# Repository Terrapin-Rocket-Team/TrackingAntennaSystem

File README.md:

# TrackingAntennaSystem
Repository will store all resources for the tracking antenna system which will dynamically point at the rocket mid-flight.

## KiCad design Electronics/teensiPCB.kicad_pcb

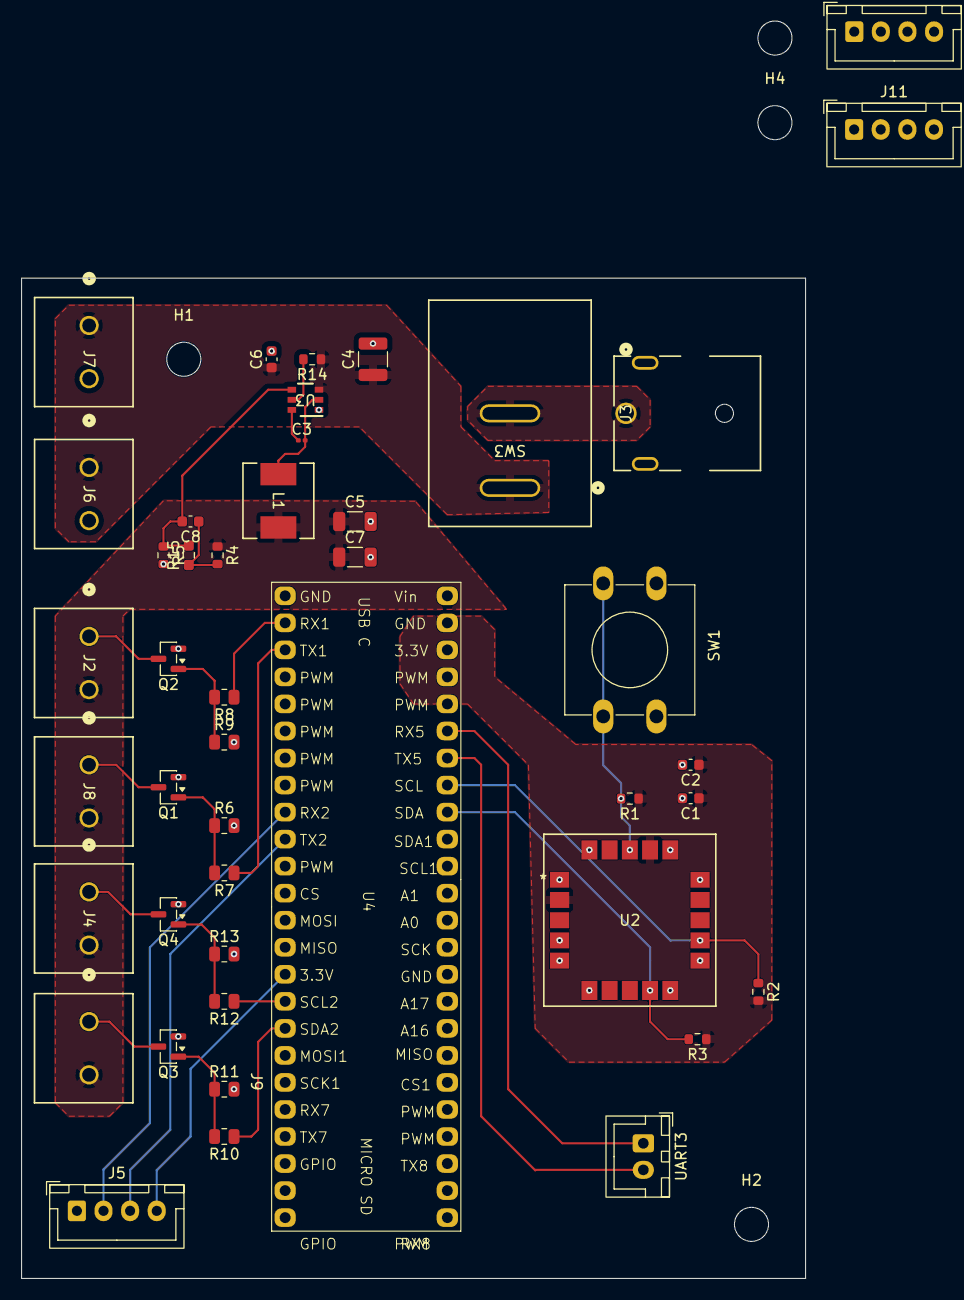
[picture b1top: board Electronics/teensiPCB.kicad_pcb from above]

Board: 2 copper layers, 73.7 x 94.0 mm, 48 parts (0 on the bottom side), 31 nets.

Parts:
C1: 0.1uF; C_0603_1608Metric
C2: 1uF; C_0603_1608Metric
C3: .1 uF; C_0201_0603Metric
C4: 10 uF; C_1210_3225Metric
C5, C7: 22 uF; C_1206_3216Metric
C6: .1 uF; C_0603_1608Metric
C8: 75 pF; C_0603_1608Metric
H1, H2, H3, H4: MountingHole; MountingHole_3.2mm_M3
J2, J8: 5V_logic_1; CONN_1935161_PXC
J3: Jack-DC; CONN1x2_PJ-082BH_CUD
J4, J9: 5V_logic_2; CONN_1935161_PXC
J5: UART1; JST_XH_B4B-XH-A_1x04_P2.50mm_Vertical
J6, J7: 24V_power_output; CONN_1935161_PXC
J10: UART2; JST_XH_B4B-XH-A_1x04_P2.50mm_Vertical
J11: 12C; JST_XH_B4B-XH-A_1x04_P2.50mm_Vertical
L1: 15 uH; IND_PCC-M0630M-LP_PAN
Q1, Q2, Q3, Q4: AO3400A; SOT-23
R1, R2, R3: 4.7k; R_0603_1608Metric
R4: 49.9 Ohms; R_0603_1608Metric
R5: 13.3 kOhms; R_0603_1608Metric
R6, R9, R11, R13: 10kO; R_0805_2012Metric
R7, R8, R10, R12: 330 Ohm; R_0805_2012Metric
R14: 510 kOhms; R_0603_1608Metric
R15: 100 kOhms; R_0603_1608Metric_Pad0.98x0.95mm_HandSolder
SW1: SW_Push; SW_PUSH-12mm
SW3: SW_SPST; SMT_1131121_EWI
U2: SAM-M10Q-00B; SAM-M10Q_UBL
U3: TPS54202HDDCR; DDC0006A_L
U4: Teensy4.1; teensy
UART3: Conn_01x02; JST_XH_B2B-XH-A_1x02_P2.50mm_Vertical

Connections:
5_dir-_1: J2.1, Q2.3 (D)
5_dir-_2: J4.1, Q4.3 (D)
5_pul-_1: J8.1, Q1.3 (D)
5_pul-_2: J9.1, Q3.3 (D)
33_dir-_1: R8.1, U4.2 (0_RX1_CRX2_CS1)
33_dir-_2: R12.1, U4.16 (24_A10_TX6_SCL2)
33_pul-_1: R7.1, U4.3 (1_TX1_CTX2_MISO1)
33_pul-_2: R10.1, U4.17 (25_A11_RX6_SDA2)
+3V3: C1.1, C2.1, J5.4, J10.4, J11.4, R1.1, R2.2, R3.1, U2.2 (V_IO), U2.17 (VCC)
+5V: C5.1, C7.1, J2.2, J4.2, J8.2, J9.2, L1.2, R4.1
+24V: C4.1, C6.1, J6.1, J7.1, R14.1, SW3.2 (B), U3.3 (VIN)
GND: C1.2, C2.2, C4.2, C5.2, C6.2, C7.2, J3.2, J5.1, J6.2, J7.2, J10.1, J11.1, Q1.2 (S), Q2.2 (S), Q3.2 (S), Q4.2 (S), R5.2, R6.2, R9.2, R11.2, R13.2, SW1.1, U2.1 (GND), U2.4 (GND), U2.5 (GND), U2.6 (GND), U2.10 (GND), U2.11 (GND), U2.15 (GND), U2.16 (GND), U2.20 (GND), U3.1 (GND)
GPS_SCL: R2.1, U2.12 (SCL), U4.41 (19_A5_SCL)
GPS_SDA: R3.2, U2.9 (SDA), U4.40 (18_A4_SDA)
unnamed: C8.1, R4.2, R15.1
unnamed: Q1.1 (G), R6.1, R7.2
unnamed: Q2.1 (G), R8.2, R9.1
unnamed: Q3.1 (G), R10.2, R11.1
unnamed: Q4.1 (G), R12.2, R13.1
unnamed: J3.1, SW3.1 (A)
unnamed: R1.2, SW1.2, U2.18 (RESET_N)
unnamed: C3.1, U3.6 (BOOT)
unnamed: R14.2, U3.5 (EN)
unnamed: C8.2, R5.1, R15.2, U3.4 (FB)
unnamed: C3.2, L1.1, U3.2 (SW)
RX1: J5.2, U4.9 (7_RX2_OUT1A)
RX_TO_GCS: J10.3, U4.43 (21_A7_RX5_BCLK1), UART3.1
SCL1: J11.2, U4.38 (16_A2_RX4_SCL1)
SDA1: J11.3, U4.39 (17_A3_TX4_SDA1)
TX1: J5.3, U4.10 (8_TX2_IN1)
TX_TO_GCS: J10.2, U4.42 (20_A6_TX5_LRCLK1), UART3.2

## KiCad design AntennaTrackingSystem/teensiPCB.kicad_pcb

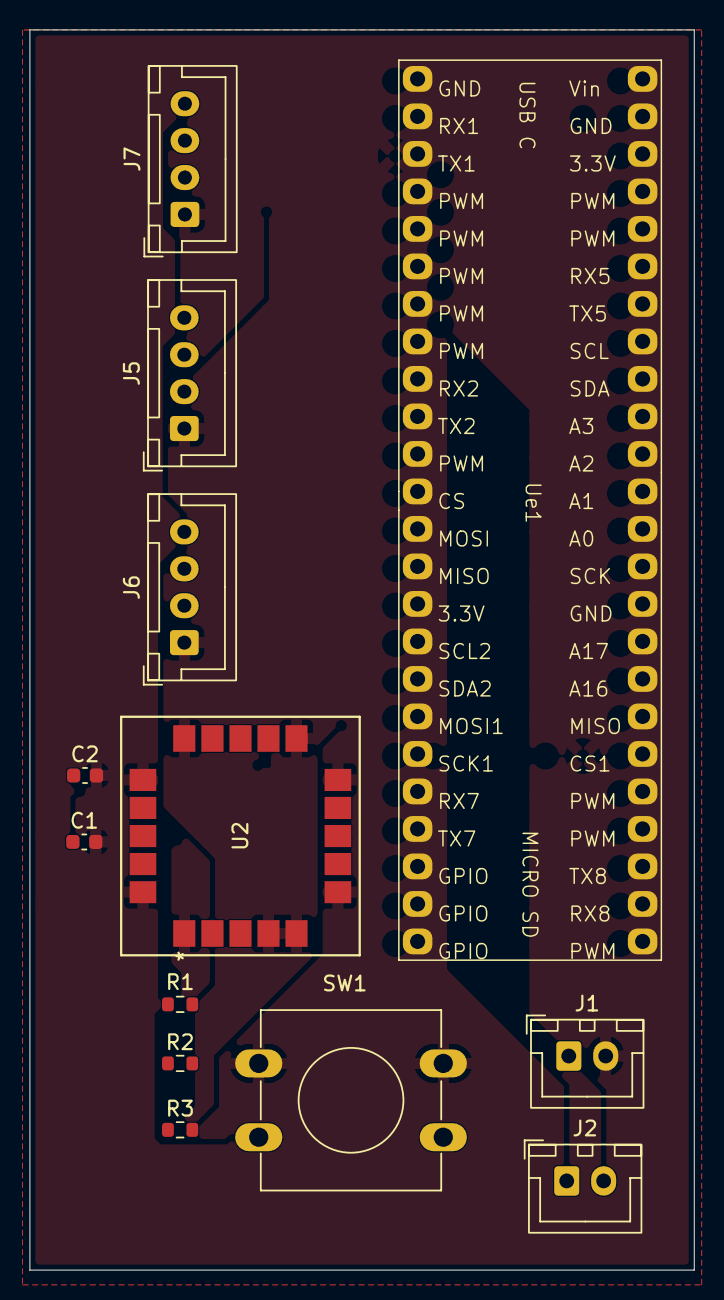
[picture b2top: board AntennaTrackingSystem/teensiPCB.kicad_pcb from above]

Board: 2 copper layers, 45.0 x 84.0 mm, 15 parts (0 on the bottom side), 13 nets, no tracks yet.

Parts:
C1: 0.1uF; C_0603_1608Metric
C2: 1uF; C_0603_1608Metric
H1, H2: MountingHole; MountingHole_3.2mm_M3
J1: screw terminal; JST_XH_B2B-XH-A_1x02_P2.50mm_Vertical
J2: Conn_01x02; JST_XH_B2B-XH-A_1x02_P2.50mm_Vertical
J5: UART1; JST_XH_B4B-XH-A_1x04_P2.50mm_Vertical
J6: UART2; JST_XH_B4B-XH-A_1x04_P2.50mm_Vertical
J7: I2C ext; JST_XH_B4B-XH-A_1x04_P2.50mm_Vertical
R1, R2, R3: 4.7k; R_0603_1608Metric
SW1: SW_Push; SW_PUSH-12mm
U2: SAM-M10Q-00B; SAM-M10Q_UBL
Ue1: Teensy4.1; teensy

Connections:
+3V3: J5.4, J6.4, J7.4, R1.1, R2.2, R3.1, U2.2 (V_IO), U2.3 (V_BCKP), U2.17 (VCC), Ue1.15 (3V3)
GND: C1.2, C2.2, J1.2, J5.1, J6.1, J7.1, SW1.1, U2.1 (GND), U2.4 (GND), U2.5 (GND), U2.6 (GND), U2.10 (GND), U2.11 (GND), U2.15 (GND), U2.16 (GND), U2.20 (GND), Ue1.1 (GND)
unnamed: C1.1, C2.1
unnamed: J1.1, J2.2
unnamed: J5.2, Ue1.2 (RX1)
unnamed: J5.3, Ue1.3 (TX1)
unnamed: J6.2, Ue1.9 (RX2)
unnamed: J6.3, Ue1.10 (TX2)
unnamed: J7.2, Ue1.16 (SCL2)
unnamed: J7.3, Ue1.17 (SDA2)
unnamed: R1.2, SW1.2, U2.18 (RESET_N)
unnamed: R2.1, U2.12 (SCL), Ue1.38 (SCL)
unnamed: R3.2, U2.9 (SDA), Ue1.39 (SDA)

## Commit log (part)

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2025-09-18 added old code in folder for future reference
2025-10-22 updates
    added checkign max angular accel/max rocket acceleration dynamics
2025-10-24 chanegs
2026-03-24 did the data reporter
    copied a lot form astra, trying to clean thing sup for our system
2026-03-25 Start of Prediction horizon architecture
2026-03-25 implemented some datareporter methods
2026-03-26 Initial PCB
2026-03-26 pcb updates
2026-03-26 Finished implementing DataReporter methods in cpp and inline file.
2026-03-26 Revert "Feature/data reporter implementations"
2026-03-26 Removed Target Prediction folder and stored locally to clean up main merge. Will add back from new branch.
2026-03-26 Added TargetPredict folder back on new branch
2026-03-27 1st schematic built and added footprints
2026-03-28 Cleaned up formatting and implemented propagate method
2026-03-28 comments for Jack
    Done on 3/28/2026
2026-03-28 responded to Div's comments: deleted RadioMeasurement, and added comments + other small things probably
2026-03-29 schematic review changes
2026-03-29 correct connector footprint
2026-03-29 cleanup
2026-03-30 back to I2C and other small updates
2026-03-30 final changes
2026-03-30 forgot tracks
2026-03-31 ground plane changes
    added ground plane
2026-03-31 ground plane chanegs
    changed ground plane
2026-03-31 changes
    added battery chnages
2026-03-31 added simple data reporter functionality
2026-03-31 Added math library and modified namespace
2026-03-31 Added GPS Folder, no mods needed.
2026-04-01 small changes
    added comments on where you should look
2026-04-01 update pcb slightly
2026-04-05 adding gps code
    to integrate gps into ats
2026-04-06 Added data logging methods and supplementary classes
2026-04-07 Added circbuffer datatype from astra utilites for use in the logging classes.
2026-04-08 Implemented Retrieval classes
2026-04-09 Changes for Isar
    1. Remove USB log
    2. Add SD Card log
    3. Organize the support classes (have diff folder) -> make all the log sink files in their own respective folders
    4. Make changes as noted in comments
2026-04-17 Footprint corrections
2026-04-18 Add files via upload
    SAM M10Q footprint
2026-04-19 added miscellaneous folder and imported teensy footprint
2026-04-21 moutning holes and corrections
    added mounting holes, still would want a better footprint for the teensy
2026-04-21 teensy footprint
    I have placed the correct teensy footprint that I got from the SRAD-Avionics Apollo folder
2026-04-21 teensy footprint
    forgot to save
2026-04-21 added gps stuff
    peeled back some layers of abstraction astra has to make stuff easier, only have one gps.
2026-04-22 started main
    using parts of astra for main, might hold off until the end for the entire actuator code
2026-04-23 updated footprint
2026-04-23 build conflicts
2026-04-27 build corrections
2026-04-27 changed file name for readability
2026-04-27 build conflicts
    changed some of the i log sink and stuff
2026-04-27 rerouted include statements.
2026-04-29 implemented gps to local coordinates from astra. Untested
2026-04-29 added a teeny testign script
2026-04-30 added a basic terminal logging system. formatting looks weird, but the basic architecture to get from hardware is implemented.
2026-04-30 fixing this branch
2026-04-30 fixing repo
2026-04-30 quick update
2026-05-01 footprint text and mounting holes
2026-05-02 quick fixes
2026-05-03 silkscreen changes
2026-05-04 SAM updates
    added everything
2026-05-04 Code review for Anthony
    Some changes, read through the comments
2026-05-04 replaced the terminal printer with a fake sensor-based data reporter. successfully uploaded and ran in monitor.
2026-05-05 review updates
    for sam m10q
2026-05-06 revision
    changed a couple of file names, small changes need to be made but its mainly fine:
2026-05-06 more changes
    columns, scalers at altitdue, and hr offsets updated
2026-05-07 one last thing, but gps is done
2026-05-07 small changes
2026-05-07 fixing
2026-05-10 replaced main.cpp with serial logging system
2026-05-10 testign sd card
2026-05-10 motor control
    started motor control flow, need to find a repository that probably already has all of this stuff
2026-05-11 fixing extractiion
    thinking i was gonna take gsdata adn aprstelem stuff and extract into a state matrix
2026-05-20 sanity test and set_angle functions
2026-05-20 Propogation step
    Will use a dead reckoning model, don't have info of noise matrix or anythgin like that
2026-05-21 changes
    updates for matt's first run through on motor control logic
2026-05-21 changes, need to find a way to detect launch
    having some troubles on figuring out how to detect launch so we can start guessing the rocket's altitude. The horizontal and vertical velocity components seem fine.
2026-05-21 motorpins changes
2026-05-22 pushed sanity
2026-05-22 del sanity test
2026-05-22 moved sanity test - now converter test
2026-05-22 Updated the extract and propogate
    Now it will use the dynamics of the rokcet until it receives the first telemetry packet, then it starts using actual data.
2026-05-22 changed motor pins
2026-05-22 class MotorPins defined
2026-05-22 changed motor pins class a bit
2026-05-23 needed changes
    Creating backend, flattening down Istorage and Ifile because we will only use the teensy and maybe internal flash (doubt it)
2026-05-24 changes for matt
    some updates; written in comments
2026-05-24 compilation errors all gone
    All that's left to do is the main.
2026-05-24 updated set_angle and other motorpins functions
2026-05-25 code review for matt
2026-05-26 added cooridinate conversion
    This is to convert from given x, y, z distance away, how much the motors have to move
2026-05-27 minor changes
2026-06-02 started main
    matt, check comment within motorpins cpp file
2026-06-02 theta changes
2026-06-03 temp changes
2026-06-03 motor changes and testing
2026-06-05 working on motors
2026-06-07 created atsmain.cpp
    this is the main file for the entire system
2026-06-08 Finished Motor code
2026-06-10 changes
    need to test main fi someone coould, also need to see if we receive an aprstelem object?
2026-06-20 stm32 led test
